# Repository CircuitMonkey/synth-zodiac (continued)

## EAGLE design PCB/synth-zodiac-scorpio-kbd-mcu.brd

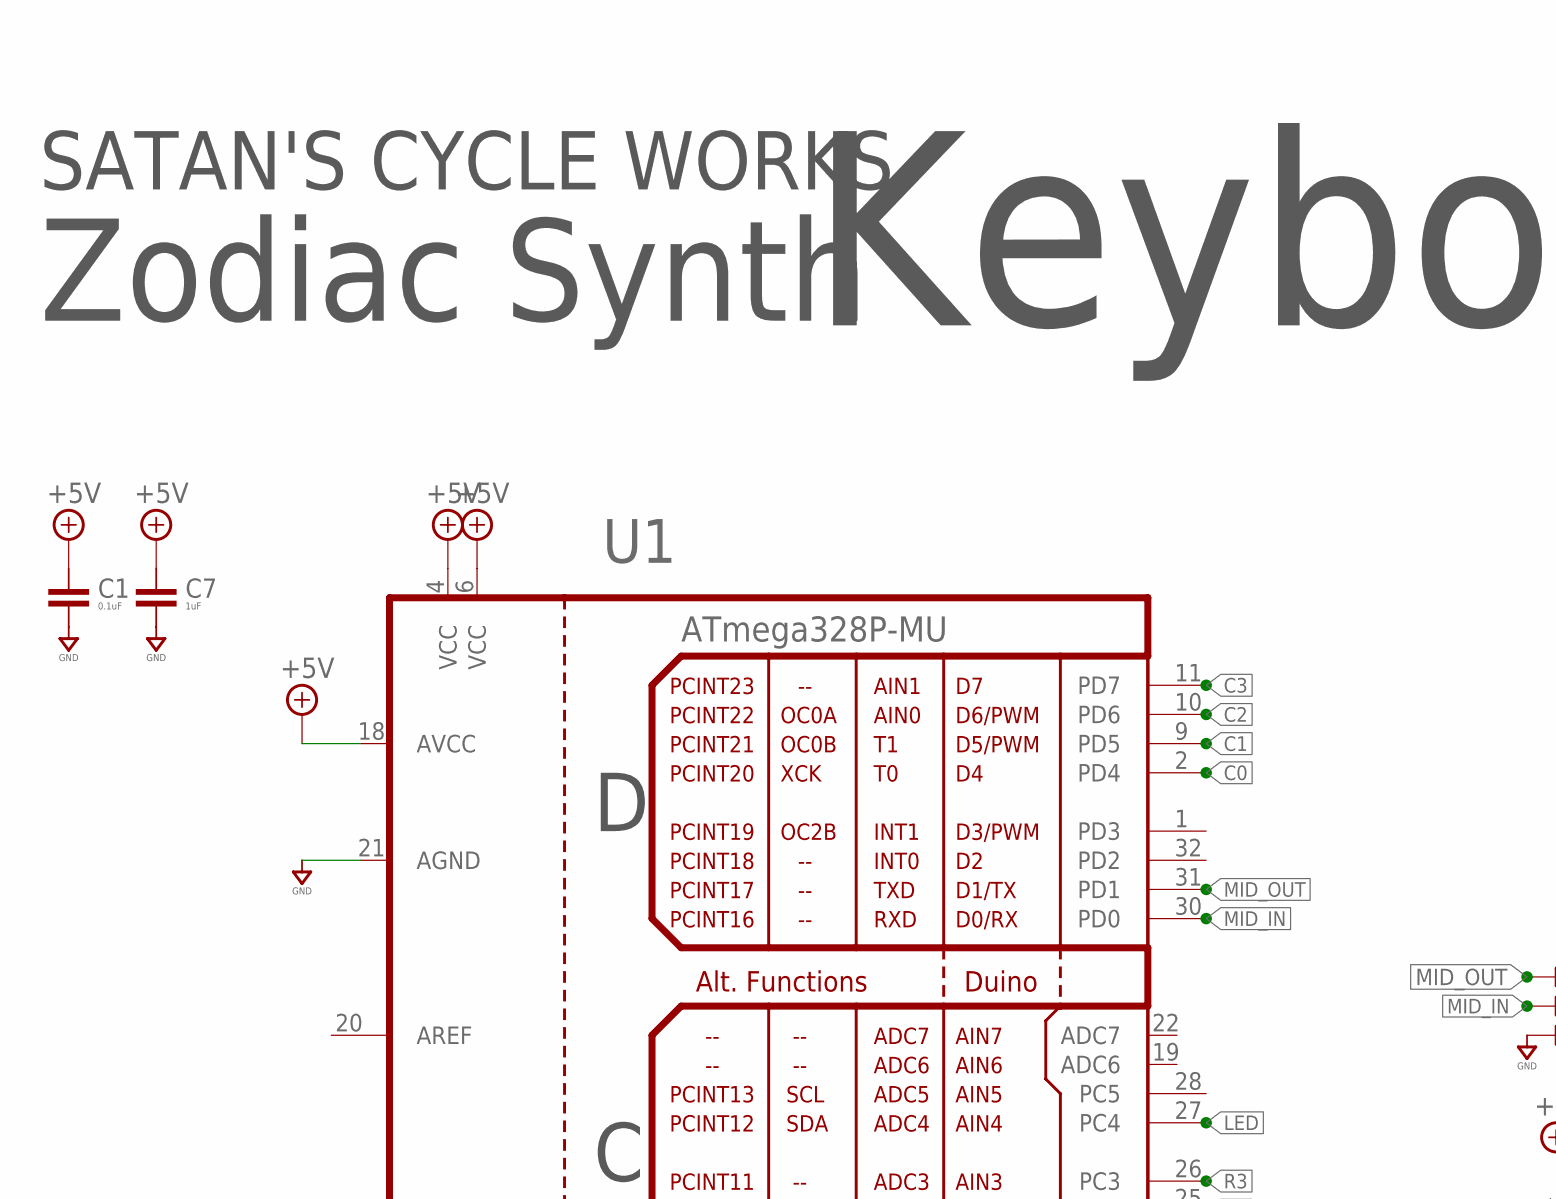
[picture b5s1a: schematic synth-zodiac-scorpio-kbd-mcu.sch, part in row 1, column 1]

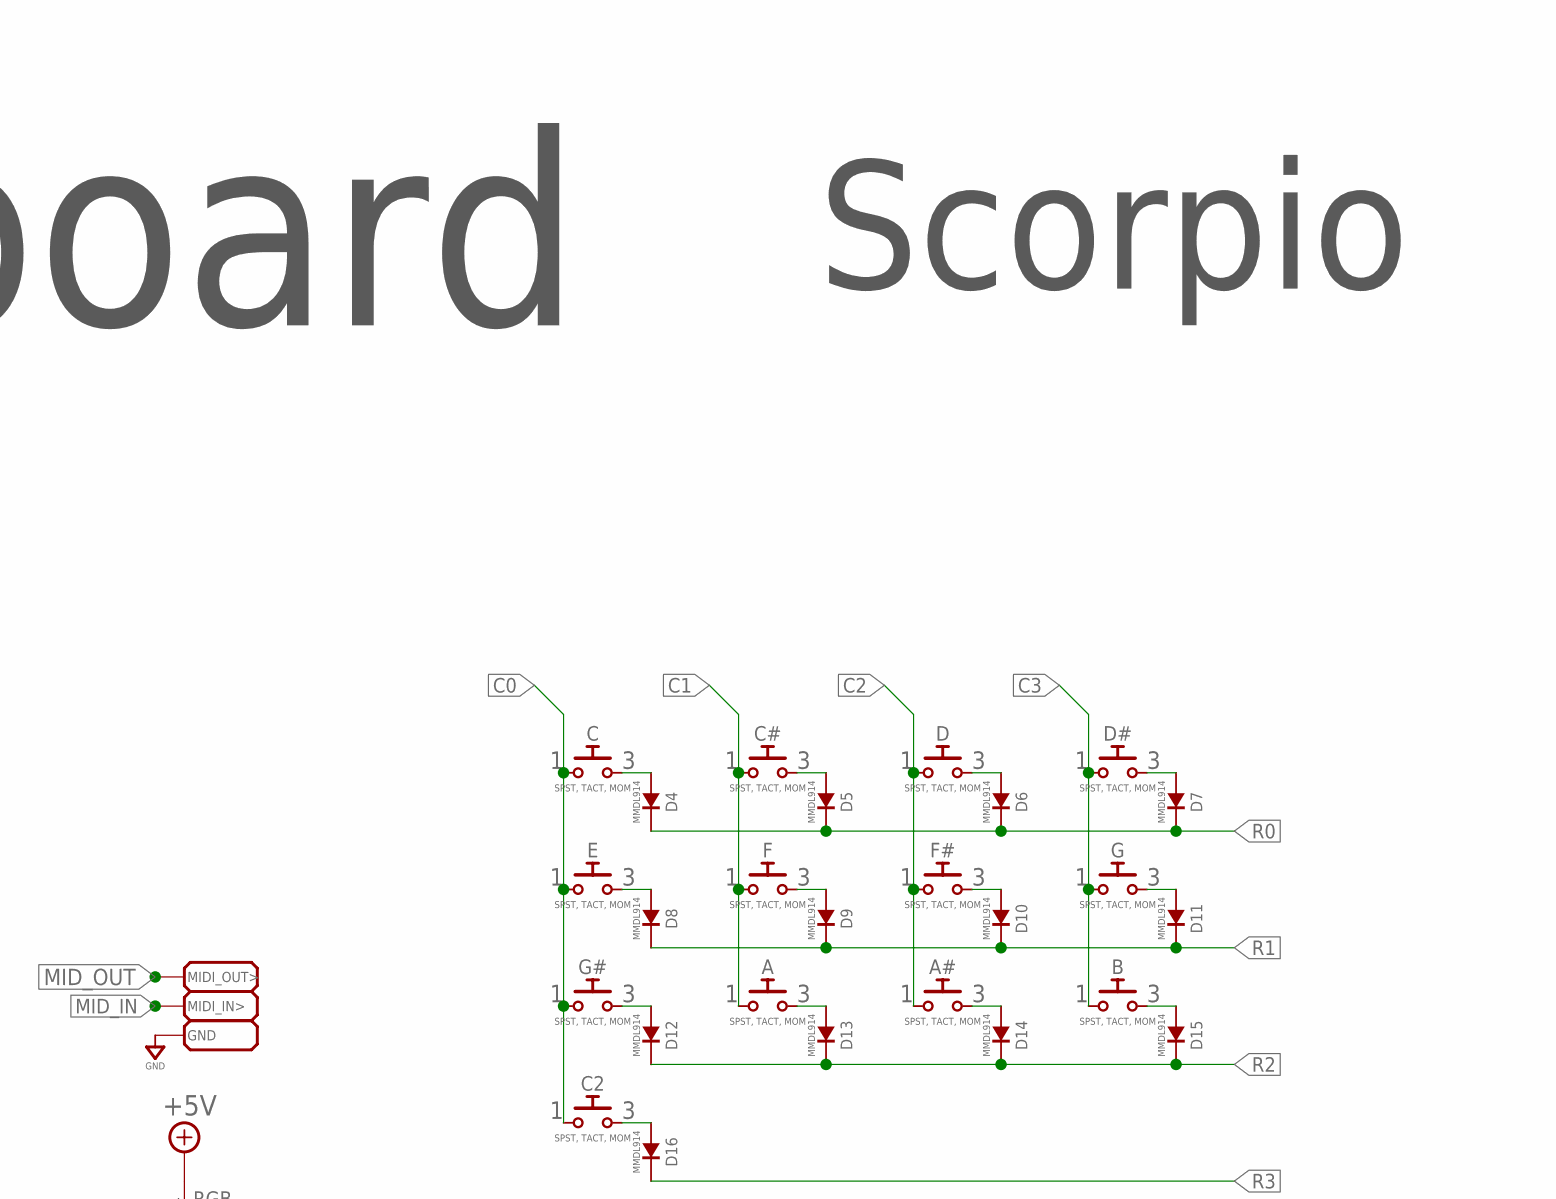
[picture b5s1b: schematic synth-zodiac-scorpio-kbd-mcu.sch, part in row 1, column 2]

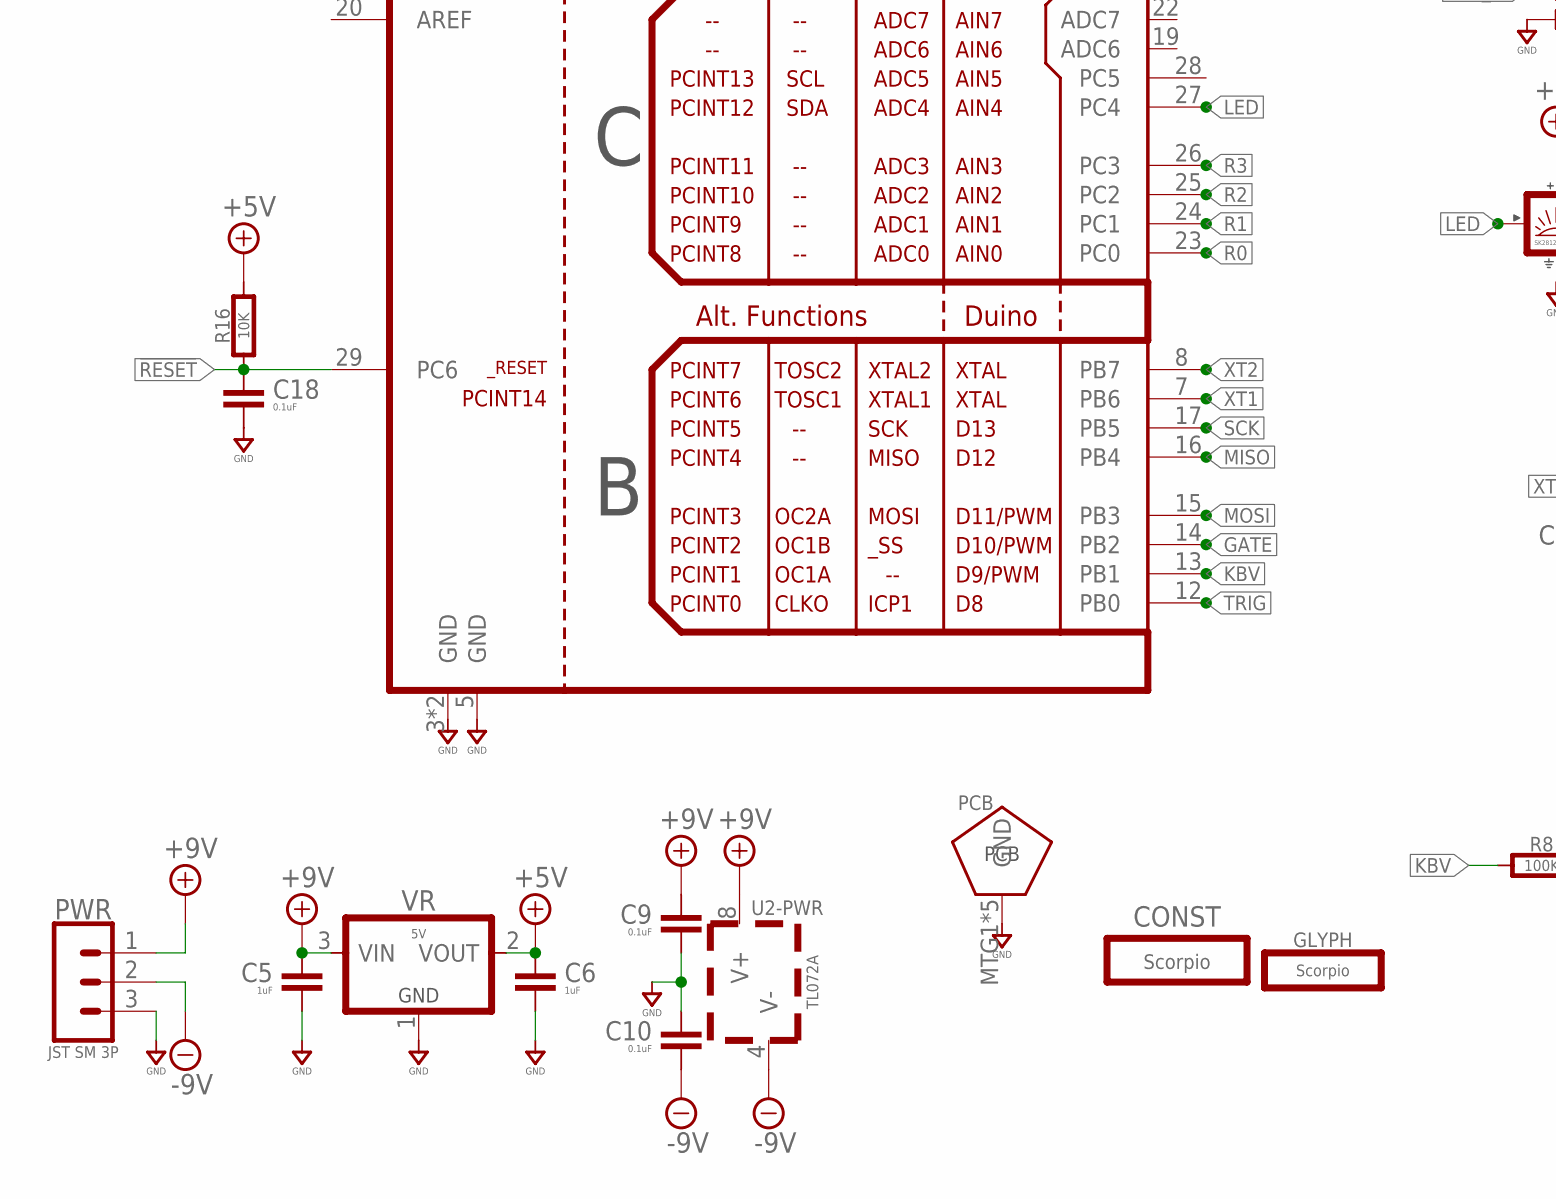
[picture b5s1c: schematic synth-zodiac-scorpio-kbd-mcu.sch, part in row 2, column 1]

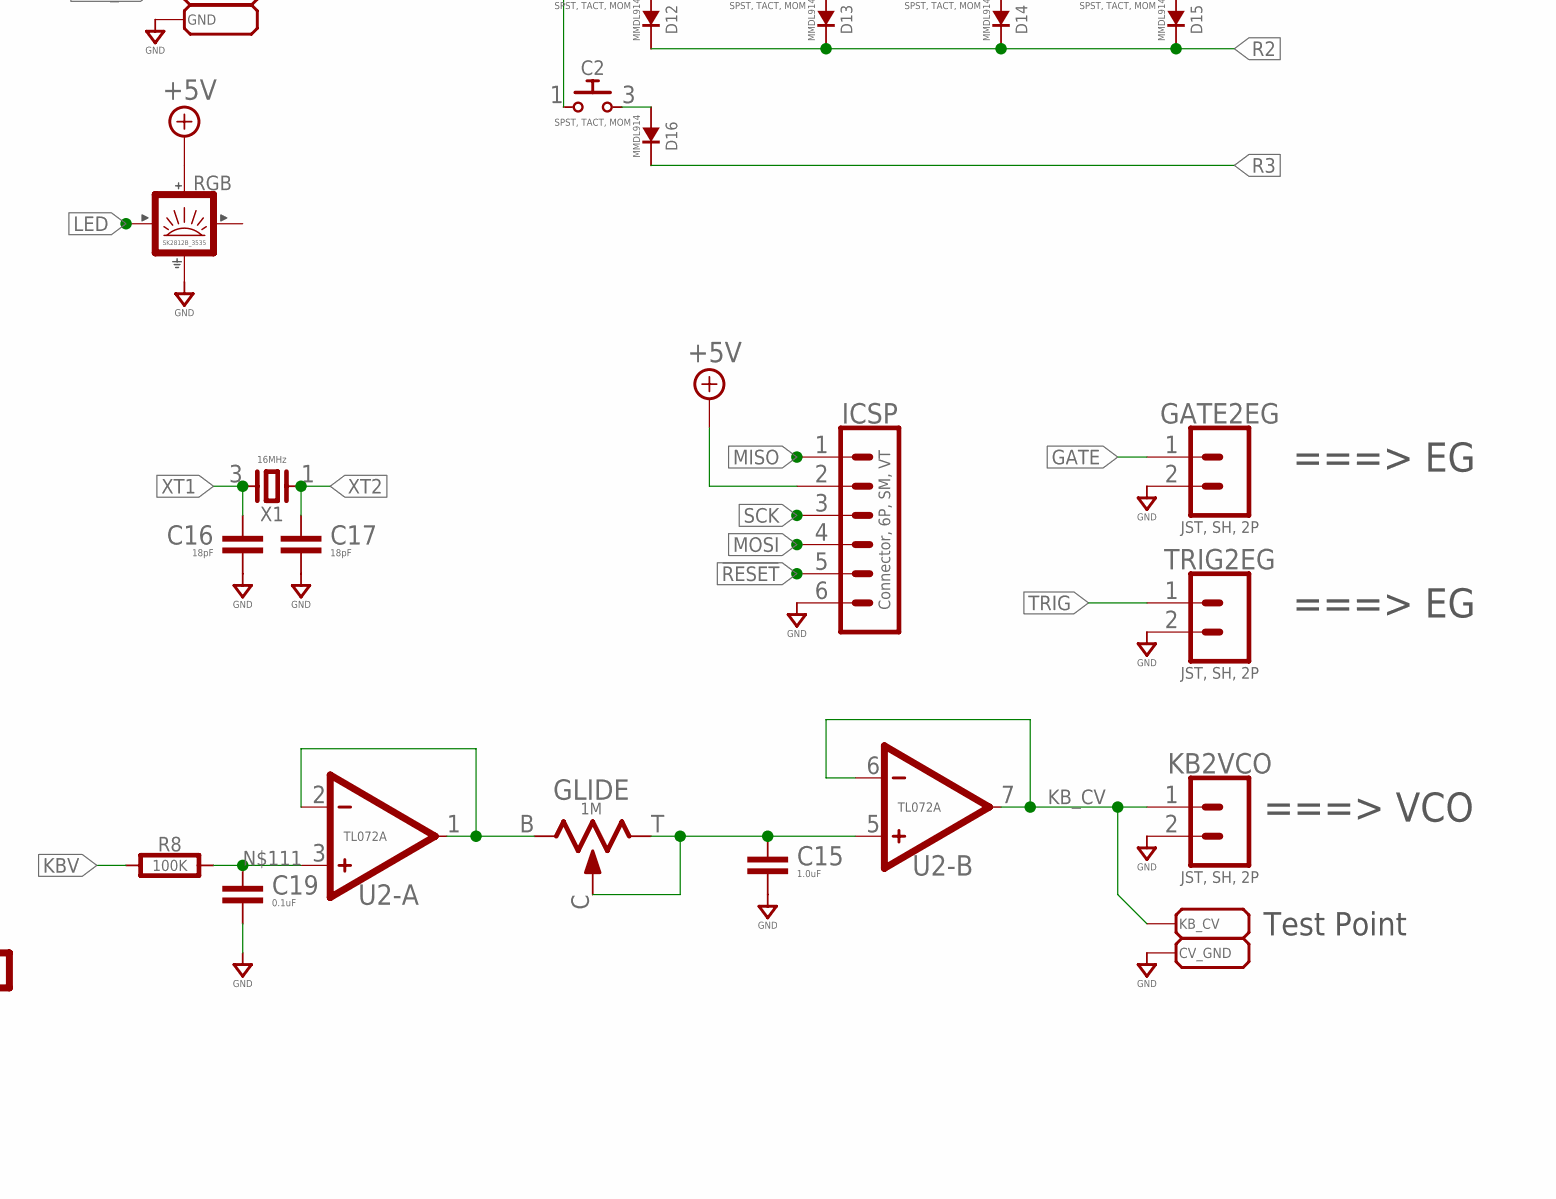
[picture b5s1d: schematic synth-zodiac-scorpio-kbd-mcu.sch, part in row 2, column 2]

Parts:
A: SPST, TACT, MOM; B3FS-BACKMOUNT
A#: SPST, TACT, MOM; B3FS-BACKMOUNT
B: SPST, TACT, MOM; B3FS-BACKMOUNT
C, C2: SPST, TACT, MOM; B3FS-BACKMOUNT
C1, C9, C10, C18, C19: 0.1uF; 0603-CAP
C5, C6, C7: 1uF; 0603-CAP
C15: 1.0uF; 0603-CAP
C16, C17: 18pF; 0603-CAP
C#: SPST, TACT, MOM; B3FS-BACKMOUNT
CONST: Scorpio; SCORPIO-CONST
CV_GND: PAD-70X70SMD-070X070; SMD-070MIL
D: SPST, TACT, MOM; B3FS-BACKMOUNT
D4, D5, D6, D7, D8, D9, D10, D11, D12, D13, D14, D15, D16: MMDL914; SOD-323
D#: SPST, TACT, MOM; B3FS-BACKMOUNT
E: SPST, TACT, MOM; B3FS-BACKMOUNT
F: SPST, TACT, MOM; B3FS-BACKMOUNT
F#: SPST, TACT, MOM; B3FS-BACKMOUNT
G: SPST, TACT, MOM; B3FS-BACKMOUNT
G#: SPST, TACT, MOM; B3FS-BACKMOUNT
GATE2EG: JST, SH, 2P; BM02B-SRSS-TB
GLIDE: 1M; POT-RV9110
GLYPH: Scorpio; SCORPIO-GLYPH
GND: PAD-70X70SMD-070X070; SMD-070MIL
ICSP: Connector, 6P, SM, VT; BM06B-SRSS-TB
KB2VCO: JST, SH, 2P; BM02B-SRSS-TB
KB_CV: PAD-70X70SMD-070X070; SMD-070MIL
MIDI_IN>: PAD-70X70SMD-070X070; SMD-070MIL
MIDI_OUT>: PAD-70X70SMD-070X070; SMD-070MIL
PCB: PCB FAB; PENTAGON-40MM-RAD
PWR: JST SM 3P; BM03B-SRSS-TB
R8: 100K; 0603-RES
R16: 10K; 0603-RES
RGB: SK2812B_3535; SMD_3535
TRIG2EG: JST, SH, 2P; BM02B-SRSS-TB
U1: ATmega328P-MU; MLF32
U2: TL072A; SOP08
VR: 5V; SOT-23
X1: 16MHz; 32X25

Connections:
!RESET: C18.1, ICSP.5, R16.1, U1.29 (PC6)
+5V: C1.1, C6.1, C7.1, ICSP.2, R16.2, RGB.4 (VDD), U1.4 (VCC), U1.6 (VCC), U1.18 (AVCC), VR.2 (VOUT)
+9V: C5.1, C9.1, PWR.1, U2.8 (V+), VR.3 (VIN)
-9V: C10.2, PWR.2, U2.4 (V-)
C0: C.1, C2.1, E.1, G#.1, U1.2 (PD4)
C1: A.1, C#.1, F.1, U1.9 (PD5)
C2: A#.1, D.1, F#.1, U1.10 (PD6)
C3: B.1, D#.1, G.1, U1.11 (PD7)
GATE: GATE2EG.1, U1.14 (PB2)
GND: C1.2, C5.2, C6.2, C7.2, C9.2, C10.1, C15.2, C16.2, C17.2, C18.2, C19.2, CV_GND.1, GATE2EG.2, GND.1, ICSP.6, KB2VCO.2, PCB.MTG1, PCB.MTG2, PCB.MTG3, PCB.MTG4, PCB.MTG5, PWR.3, RGB.2 (GND), TRIG2EG.2, U1.3 (GND), U1.5 (GND), U1.21 (AGND), U1.PAD (GND), VR.1 (GND)
KBV: R8.1, U1.13 (PB1)
KB_CV: KB2VCO.1, KB_CV.1, U2.6 (-), U2.7 (OUT)
LED: RGB.3 (IN), U1.27 (PC4)
MID_IN: MIDI_IN>.1, U1.30 (PD0)
MID_OUT: MIDI_OUT>.1, U1.31 (PD1)
MISO: ICSP.1, U1.16 (PB4)
MOSI: ICSP.4, U1.15 (PB3)
unnamed: C19.1, R8.2, U2.3 (+)
unnamed: GLIDE.B (1), U2.1 (OUT), U2.2 (-)
unnamed: C.3 (2), D4.A
unnamed: C15.1, GLIDE.C (2), GLIDE.T (3), U2.5 (+)
unnamed: C#.3 (2), D5.A
unnamed: D.3 (2), D6.A
unnamed: D7.A, D#.3 (2)
unnamed: D8.A, E.3 (2)
unnamed: D9.A, F.3 (2)
unnamed: D10.A, F#.3 (2)
unnamed: D11.A, G.3 (2)
unnamed: D12.A, G#.3 (2)
unnamed: A.3 (2), D13.A
unnamed: A#.3 (2), D14.A
unnamed: B.3 (2), D15.A
unnamed: C2.3 (2), D16.A
R0: D4.K, D5.K, D6.K, D7.K, U1.23 (PC0)
R1: D8.K, D9.K, D10.K, D11.K, U1.24 (PC1)
R2: D12.K, D13.K, D14.K, D15.K, U1.25 (PC2)
R3: D16.K, U1.26 (PC3)
SCK: ICSP.3, U1.17 (PB5)
TRIG: TRIG2EG.1, U1.12 (PB0)
XT1: C16.1, U1.7 (PB6), X1.3
XT2: C17.1, U1.8 (PB7), X1.1

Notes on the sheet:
===> EG
===> VCO
Test Point
Keyboard
Zodiac Synth
Scorpio
SATAN'S CYCLE WORKS

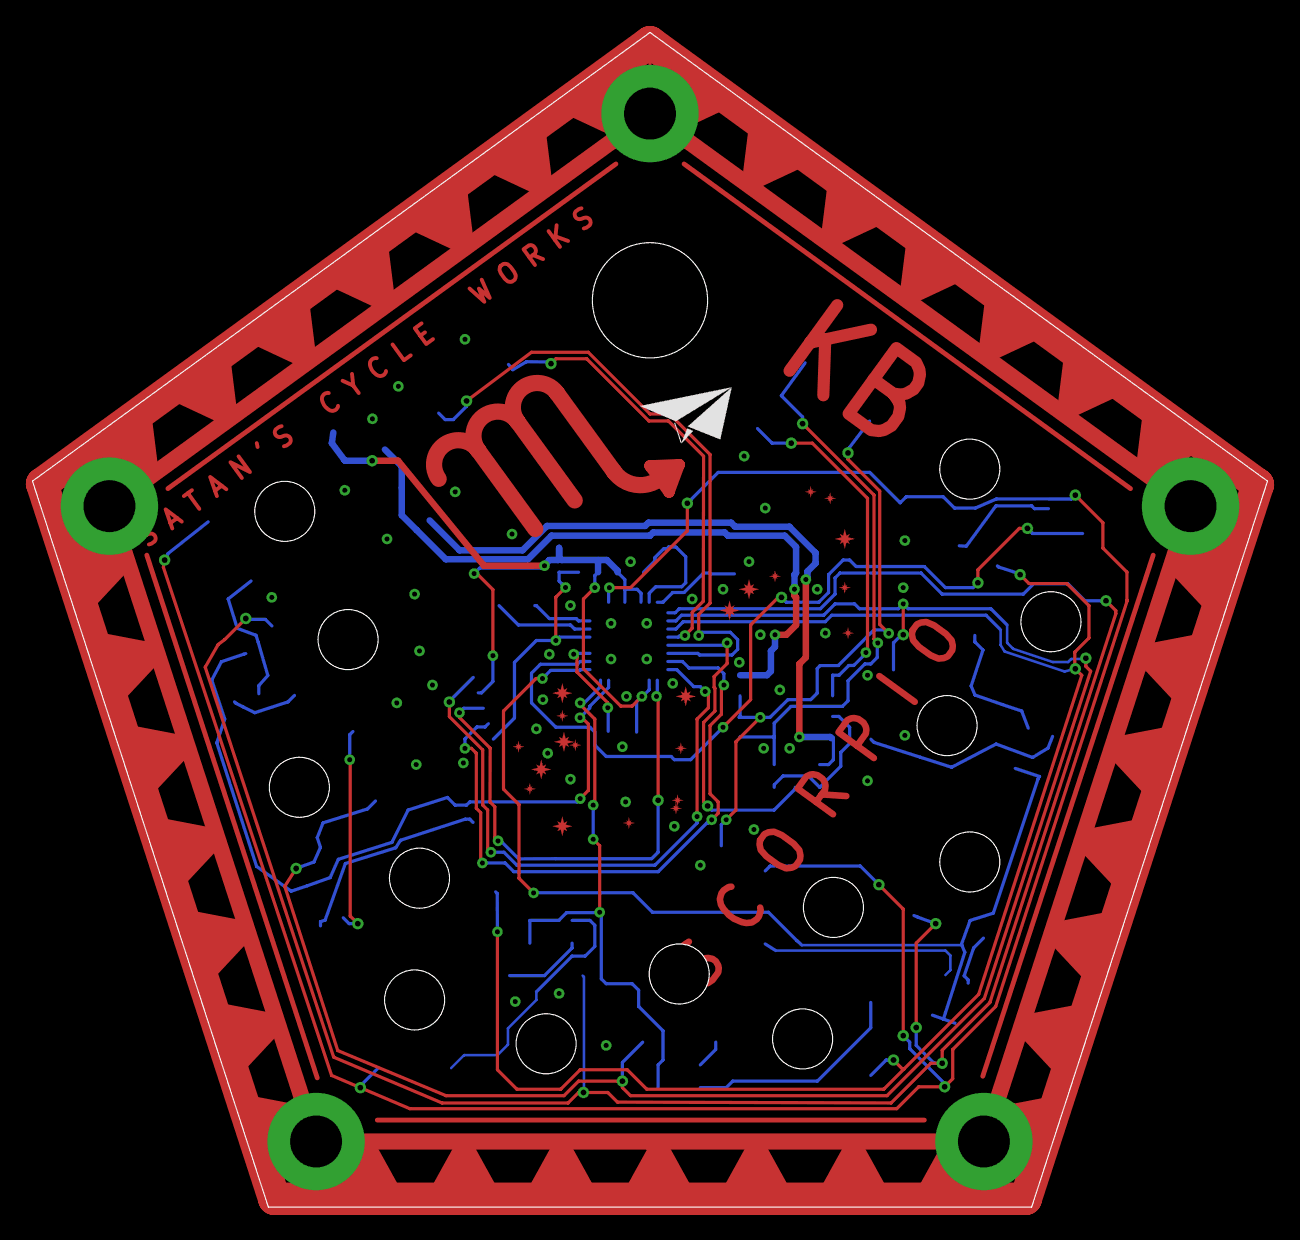
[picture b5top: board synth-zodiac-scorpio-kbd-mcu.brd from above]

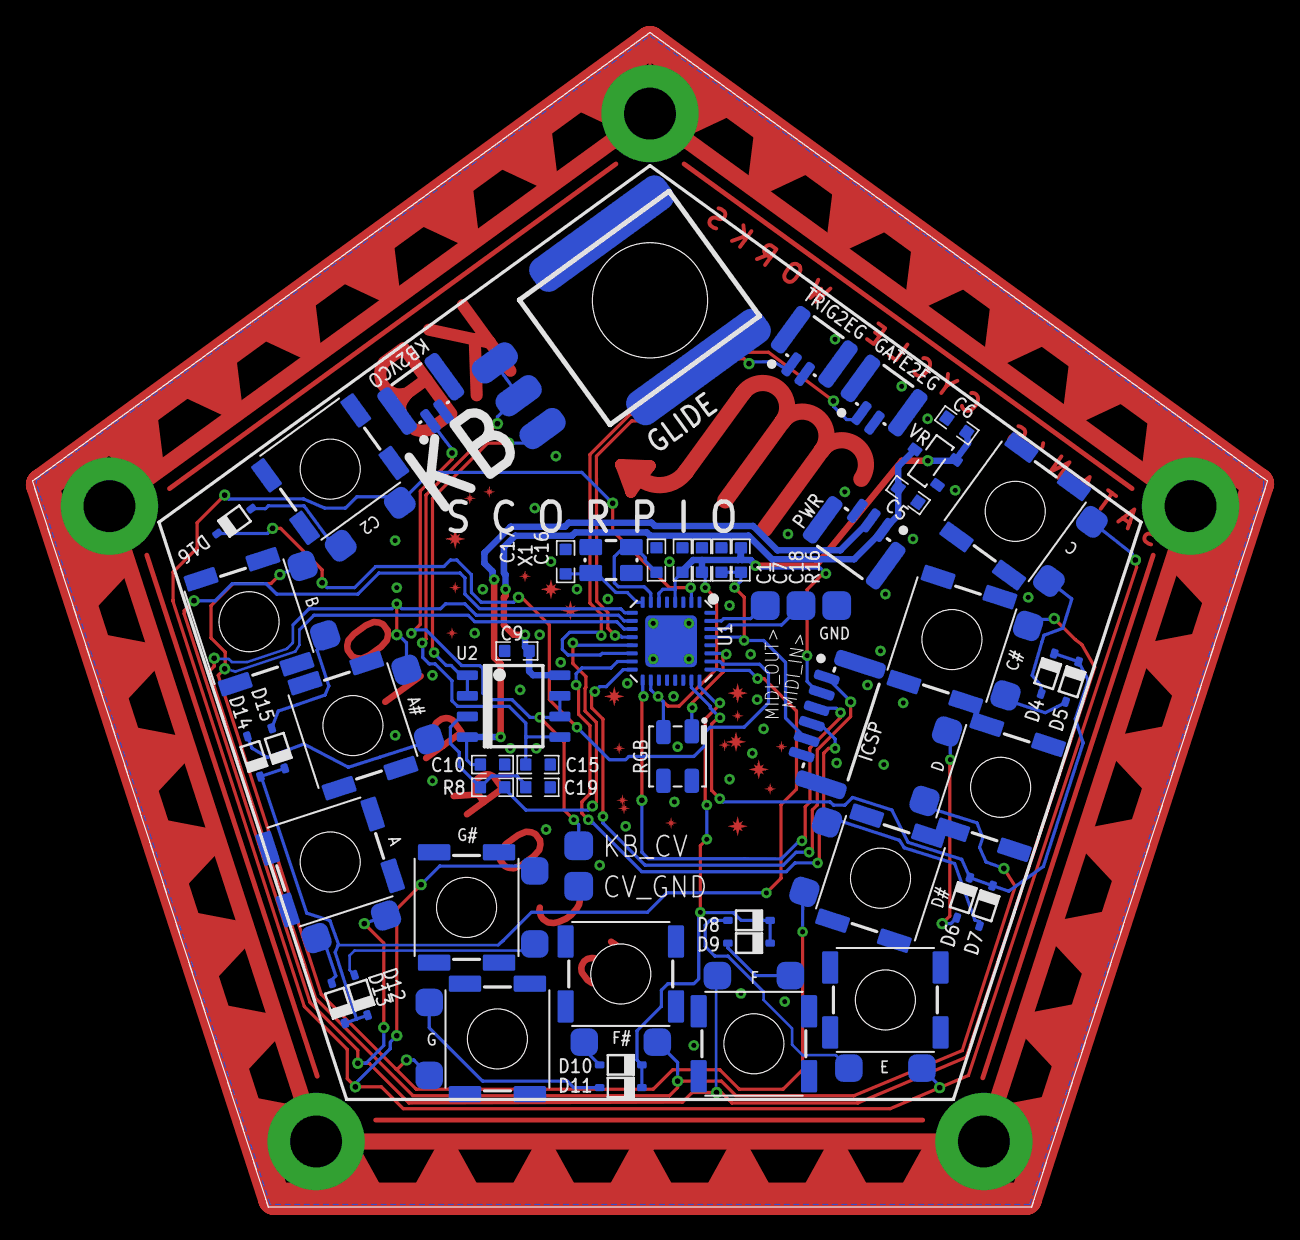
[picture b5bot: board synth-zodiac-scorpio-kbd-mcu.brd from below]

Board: 2 copper layers, 76.1 x 72.4 mm, 58 parts (42 on the bottom side), 41 nets.

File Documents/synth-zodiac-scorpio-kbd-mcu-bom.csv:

"Part";"Value";"Device";"Package";"Description";"COST01";"COST10";"COST100";"MFR";"MPN";"MPN2";"OC_MOUSER";"OC_SEEED";"SKU";"VALUE";
"A";"SPST, TACT, MOM";"PUSHBTN-MOMB3FS-BLIND";"B3FS-BACKMOUNT";"Pushbutton Switch";"0.15";"0.12";"0.09";"CK";"B3FS";"Tayda A-3961(2.3mm), A-5134(3.14mm,RA)";"";"";"";"SPST, TACT, MOM";
"A#";"SPST, TACT, MOM";"PUSHBTN-MOMB3FS-BLIND";"B3FS-BACKMOUNT";"Pushbutton Switch";"0.15";"0.12";"0.09";"CK";"B3FS";"Tayda A-3961(2.3mm), A-5134(3.14mm,RA)";"";"";"";"SPST, TACT, MOM";
"B";"SPST, TACT, MOM";"PUSHBTN-MOMB3FS-BLIND";"B3FS-BACKMOUNT";"Pushbutton Switch";"0.15";"0.12";"0.09";"CK";"B3FS";"Tayda A-3961(2.3mm), A-5134(3.14mm,RA)";"";"";"";"SPST, TACT, MOM";
"C";"SPST, TACT, MOM";"PUSHBTN-MOMB3FS-BLIND";"B3FS-BACKMOUNT";"Pushbutton Switch";"0.15";"0.12";"0.09";"CK";"B3FS";"Tayda A-3961(2.3mm), A-5134(3.14mm,RA)";"";"";"";"SPST, TACT, MOM";
"C#";"SPST, TACT, MOM";"PUSHBTN-MOMB3FS-BLIND";"B3FS-BACKMOUNT";"Pushbutton Switch";"0.15";"0.12";"0.09";"CK";"B3FS";"Tayda A-3961(2.3mm), A-5134(3.14mm,RA)";"";"";"";"SPST, TACT, MOM";
"C1";"0.1uF";"CAPACITOR0603";"0603-CAP";"Capacitor";"0.12";"0.09";"0.05";"";"";"";"";"";"";"";
"C2";"SPST, TACT, MOM";"PUSHBTN-MOMB3FS-BLIND";"B3FS-BACKMOUNT";"Pushbutton Switch";"0.15";"0.12";"0.09";"CK";"B3FS";"Tayda A-3961(2.3mm), A-5134(3.14mm,RA)";"";"";"";"SPST, TACT, MOM";
"C5";"1uF";"CAPACITOR0603";"0603-CAP";"Capacitor";"0.12";"0.09";"0.05";"";"";"";"";"";"";"";
"C6";"1uF";"CAPACITOR0603";"0603-CAP";"Capacitor";"0.12";"0.09";"0.05";"";"";"";"";"";"";"";
"C7";"1uF";"CAPACITOR0603";"0603-CAP";"Capacitor";"0.12";"0.09";"0.05";"";"";"";"";"";"";"";
"C9";"0.1uF";"CAPACITOR0603";"0603-CAP";"Capacitor";"0.12";"0.09";"0.05";"";"";"";"";"";"";"";
"C10";"0.1uF";"CAPACITOR0603";"0603-CAP";"Capacitor";"0.12";"0.09";"0.05";"";"";"";"";"";"";"";
"C15";"1.0uF";"CAPACITOR0603";"0603-CAP";"Capacitor";"0.12";"0.09";"0.05";"";"";"";"";"";"";"";
"C16";"18pF";"CAPACITOR0603";"0603-CAP";"Capacitor";"0.12";"0.09";"0.05";"";"";"";"";"";"";"";
"C17";"18pF";"CAPACITOR0603";"0603-CAP";"Capacitor";"0.12";"0.09";"0.05";"";"";"";"";"";"";"";
"C18";"0.1uF";"CAPACITOR0603";"0603-CAP";"Capacitor";"0.12";"0.09";"0.05";"";"";"";"";"";"";"";
"C19";"0.1uF";"CAPACITOR0603";"0603-CAP";"Capacitor";"0.12";"0.09";"0.05";"";"";"";"";"";"";"";
"CONST";"Scorpio";"CONSTELLATION-SCORPIO";"SCORPIO-CONST";"Constellations";"";"";"";"";"";"";"";"";"";"Scorpio";
"CV_GND";"PAD-70X70SMD-070X070";"PAD-70X70SMD-070X070";"SMD-070MIL";"Solder Pad";"";"";"";"";"";"";"";"";"";"";
"D";"SPST, TACT, MOM";"PUSHBTN-MOMB3FS-BLIND";"B3FS-BACKMOUNT";"Pushbutton Switch";"0.15";"0.12";"0.09";"CK";"B3FS";"Tayda A-3961(2.3mm), A-5134(3.14mm,RA)";"";"";"";"SPST, TACT, MOM";
"D#";"SPST, TACT, MOM";"PUSHBTN-MOMB3FS-BLIND";"B3FS-BACKMOUNT";"Pushbutton Switch";"0.15";"0.12";"0.09";"CK";"B3FS";"Tayda A-3961(2.3mm), A-5134(3.14mm,RA)";"";"";"";"SPST, TACT, MOM";
"D4";"MMDL914";"DIODE-SWITCHING-SOD323";"SOD-323";"Diode";"";"";"";"ON Semi";"MMDL914";"";"";"";"";"MMDL914";
"D5";"MMDL914";"DIODE-SWITCHING-SOD323";"SOD-323";"Diode";"";"";"";"ON Semi";"MMDL914";"";"";"";"";"MMDL914";
"D6";"MMDL914";"DIODE-SWITCHING-SOD323";"SOD-323";"Diode";"";"";"";"ON Semi";"MMDL914";"";"";"";"";"MMDL914";
"D7";"MMDL914";"DIODE-SWITCHING-SOD323";"SOD-323";"Diode";"";"";"";"ON Semi";"MMDL914";"";"";"";"";"MMDL914";
"D8";"MMDL914";"DIODE-SWITCHING-SOD323";"SOD-323";"Diode";"";"";"";"ON Semi";"MMDL914";"";"";"";"";"MMDL914";
"D9";"MMDL914";"DIODE-SWITCHING-SOD323";"SOD-323";"Diode";"";"";"";"ON Semi";"MMDL914";"";"";"";"";"MMDL914";
"D10";"MMDL914";"DIODE-SWITCHING-SOD323";"SOD-323";"Diode";"";"";"";"ON Semi";"MMDL914";"";"";"";"";"MMDL914";
"D11";"MMDL914";"DIODE-SWITCHING-SOD323";"SOD-323";"Diode";"";"";"";"ON Semi";"MMDL914";"";"";"";"";"MMDL914";
"D12";"MMDL914";"DIODE-SWITCHING-SOD323";"SOD-323";"Diode";"";"";"";"ON Semi";"MMDL914";"";"";"";"";"MMDL914";
"D13";"MMDL914";"DIODE-SWITCHING-SOD323";"SOD-323";"Diode";"";"";"";"ON Semi";"MMDL914";"";"";"";"";"MMDL914";
"D14";"MMDL914";"DIODE-SWITCHING-SOD323";"SOD-323";"Diode";"";"";"";"ON Semi";"MMDL914";"";"";"";"";"MMDL914";
"D15";"MMDL914";"DIODE-SWITCHING-SOD323";"SOD-323";"Diode";"";"";"";"ON Semi";"MMDL914";"";"";"";"";"MMDL914";
"D16";"MMDL914";"DIODE-SWITCHING-SOD323";"SOD-323";"Diode";"";"";"";"ON Semi";"MMDL914";"";"";"";"";"MMDL914";
"E";"SPST, TACT, MOM";"PUSHBTN-MOMB3FS-BLIND";"B3FS-BACKMOUNT";"Pushbutton Switch";"0.15";"0.12";"0.09";"CK";"B3FS";"Tayda A-3961(2.3mm), A-5134(3.14mm,RA)";"";"";"";"SPST, TACT, MOM";
"F";"SPST, TACT, MOM";"PUSHBTN-MOMB3FS-BLIND";"B3FS-BACKMOUNT";"Pushbutton Switch";"0.15";"0.12";"0.09";"CK";"B3FS";"Tayda A-3961(2.3mm), A-5134(3.14mm,RA)";"";"";"";"SPST, TACT, MOM";
"F#";"SPST, TACT, MOM";"PUSHBTN-MOMB3FS-BLIND";"B3FS-BACKMOUNT";"Pushbutton Switch";"0.15";"0.12";"0.09";"CK";"B3FS";"Tayda A-3961(2.3mm), A-5134(3.14mm,RA)";"";"";"";"SPST, TACT, MOM";
"G";"SPST, TACT, MOM";"PUSHBTN-MOMB3FS-BLIND";"B3FS-BACKMOUNT";"Pushbutton Switch";"0.15";"0.12";"0.09";"CK";"B3FS";"Tayda A-3961(2.3mm), A-5134(3.14mm,RA)";"";"";"";"SPST, TACT, MOM";
"G#";"SPST, TACT, MOM";"PUSHBTN-MOMB3FS-BLIND";"B3FS-BACKMOUNT";"Pushbutton Switch";"0.15";"0.12";"0.09";"CK";"B3FS";"Tayda A-3961(2.3mm), A-5134(3.14mm,RA)";"";"";"";"SPST, TACT, MOM";
"GATE2EG";"JST, SH, 2P";"02P-SM-VT-SMT";"BM02B-SRSS-TB";"2 pin connector";"0.45";"0.4";"0.35";"JST";"BMB02B-SRSS-TB";"";"";"";"";"JST, SH, 2P";
"GLIDE";"1M";"TRIMPOT9MM_PCB_SHAFT";"POT-RV9110";"Potentiometer";"0.70";"0.60";"0.60";"Tayda";"RV9110NO-OS15A00";"";"";"";"A-5517";"";
"GLYPH";"Scorpio";"GLYPH-SCORPIO";"SCORPIO-GLYPH";"Glyph";"";"";"";"";"";"";"";"";"";"Scorpio";
"GND";"PAD-70X70SMD-070X070";"PAD-70X70SMD-070X070";"SMD-070MIL";"Solder Pad";"";"";"";"";"";"";"";"";"";"";
"ICSP";"Connector, 6P, SM, VT";"06P-SM-VT-SMT";"BM06B-SRSS-TB";"Connector, 6P";"0.60";"0.52";"0.49";"JST";"BM06-SRSS-TB";"";"";"";"";"Connector, 6P, SM, VT";
"KB2VCO";"JST, SH, 2P";"02P-SM-VT-SMT";"BM02B-SRSS-TB";"2 pin connector";"0.45";"0.4";"0.35";"JST";"BMB02B-SRSS-TB";"";"";"";"";"JST, SH, 2P";
"KB_CV";"PAD-70X70SMD-070X070";"PAD-70X70SMD-070X070";"SMD-070MIL";"Solder Pad";"";"";"";"";"";"";"";"";"";"";
"MIDI_IN>";"PAD-70X70SMD-070X070";"PAD-70X70SMD-070X070";"SMD-070MIL";"Solder Pad";"";"";"";"";"";"";"";"";"";"";
"MIDI_OUT>";"PAD-70X70SMD-070X070";"PAD-70X70SMD-070X070";"SMD-070MIL";"Solder Pad";"";"";"";"";"";"";"";"";"";"";
"PCB";"PCB FAB";"PENTAGON-40R";"PENTAGON-40MM-RAD";"Pentagram shaped PCB";"";"";"";"";"";"";"";"";"";"PCB FAB";
"PWR";"JST SM 3P";"03P-SM-VT-SMT";"BM03B-SRSS-TB";"3 pin connector";"0.60";"0.45";"0.38";"JST";"BM03B-SRSS-TB";"";"";"";"";"JST SM 3P";
"R8";"100K";"RESISTOR0603";"0603-RES";"Resistor";"0.10";"0.05";"0.02";"";"";"";"";"";"";"";
"R16";"10.0M";"RESISTOR0603";"0603-RES";"Resistor";"0.10";"0.05";"0.02";"";"";"";"";"";"";"";
"RGB";"SK2812B_3535";"SMART_LED3535";"SMD_3535";"Smart LED  SK6812  WS2812";"0.60";"0.50";"0.40";"";"";"";"";"";"";"SK2812B_3535";
"TRIG2EG";"JST, SH, 2P";"02P-SM-VT-SMT";"BM02B-SRSS-TB";"2 pin connector";"0.45";"0.4";"0.35";"JST";"BMB02B-SRSS-TB";"";"";"";"";"JST, SH, 2P";
"U1";"ATmega328P-MU";"ATMEGA328MU";"MLF32";"Atmega 328P";"";"";"";"Atmel";"atmega328p-mu";"";"556-ATMEGA328P-MU";"310010005";"";"ATmega328P-MU";
"U2";"TL072A";"DUALTL072A";"SOP08";"Dual Op-Amp";"0.65";"0.55";"0.45";"ST";"TL072A";"";"";"";"";"TL072A";
"VR";"5V";"LDO-3P--5V-SOT23";"SOT-23";"regulator 3-pin";"0.66";"0.56";"0.39";"Diodes, Inc.";"AP7387-50SA";"";"";"";"";"5V";
"X1";"16MHz";"2P3.2X2.5";"32X25";"Crystal";"";"";"";"Epson";"FA-238 16.0000MB-K3";"";"";"";"";"16MHz";

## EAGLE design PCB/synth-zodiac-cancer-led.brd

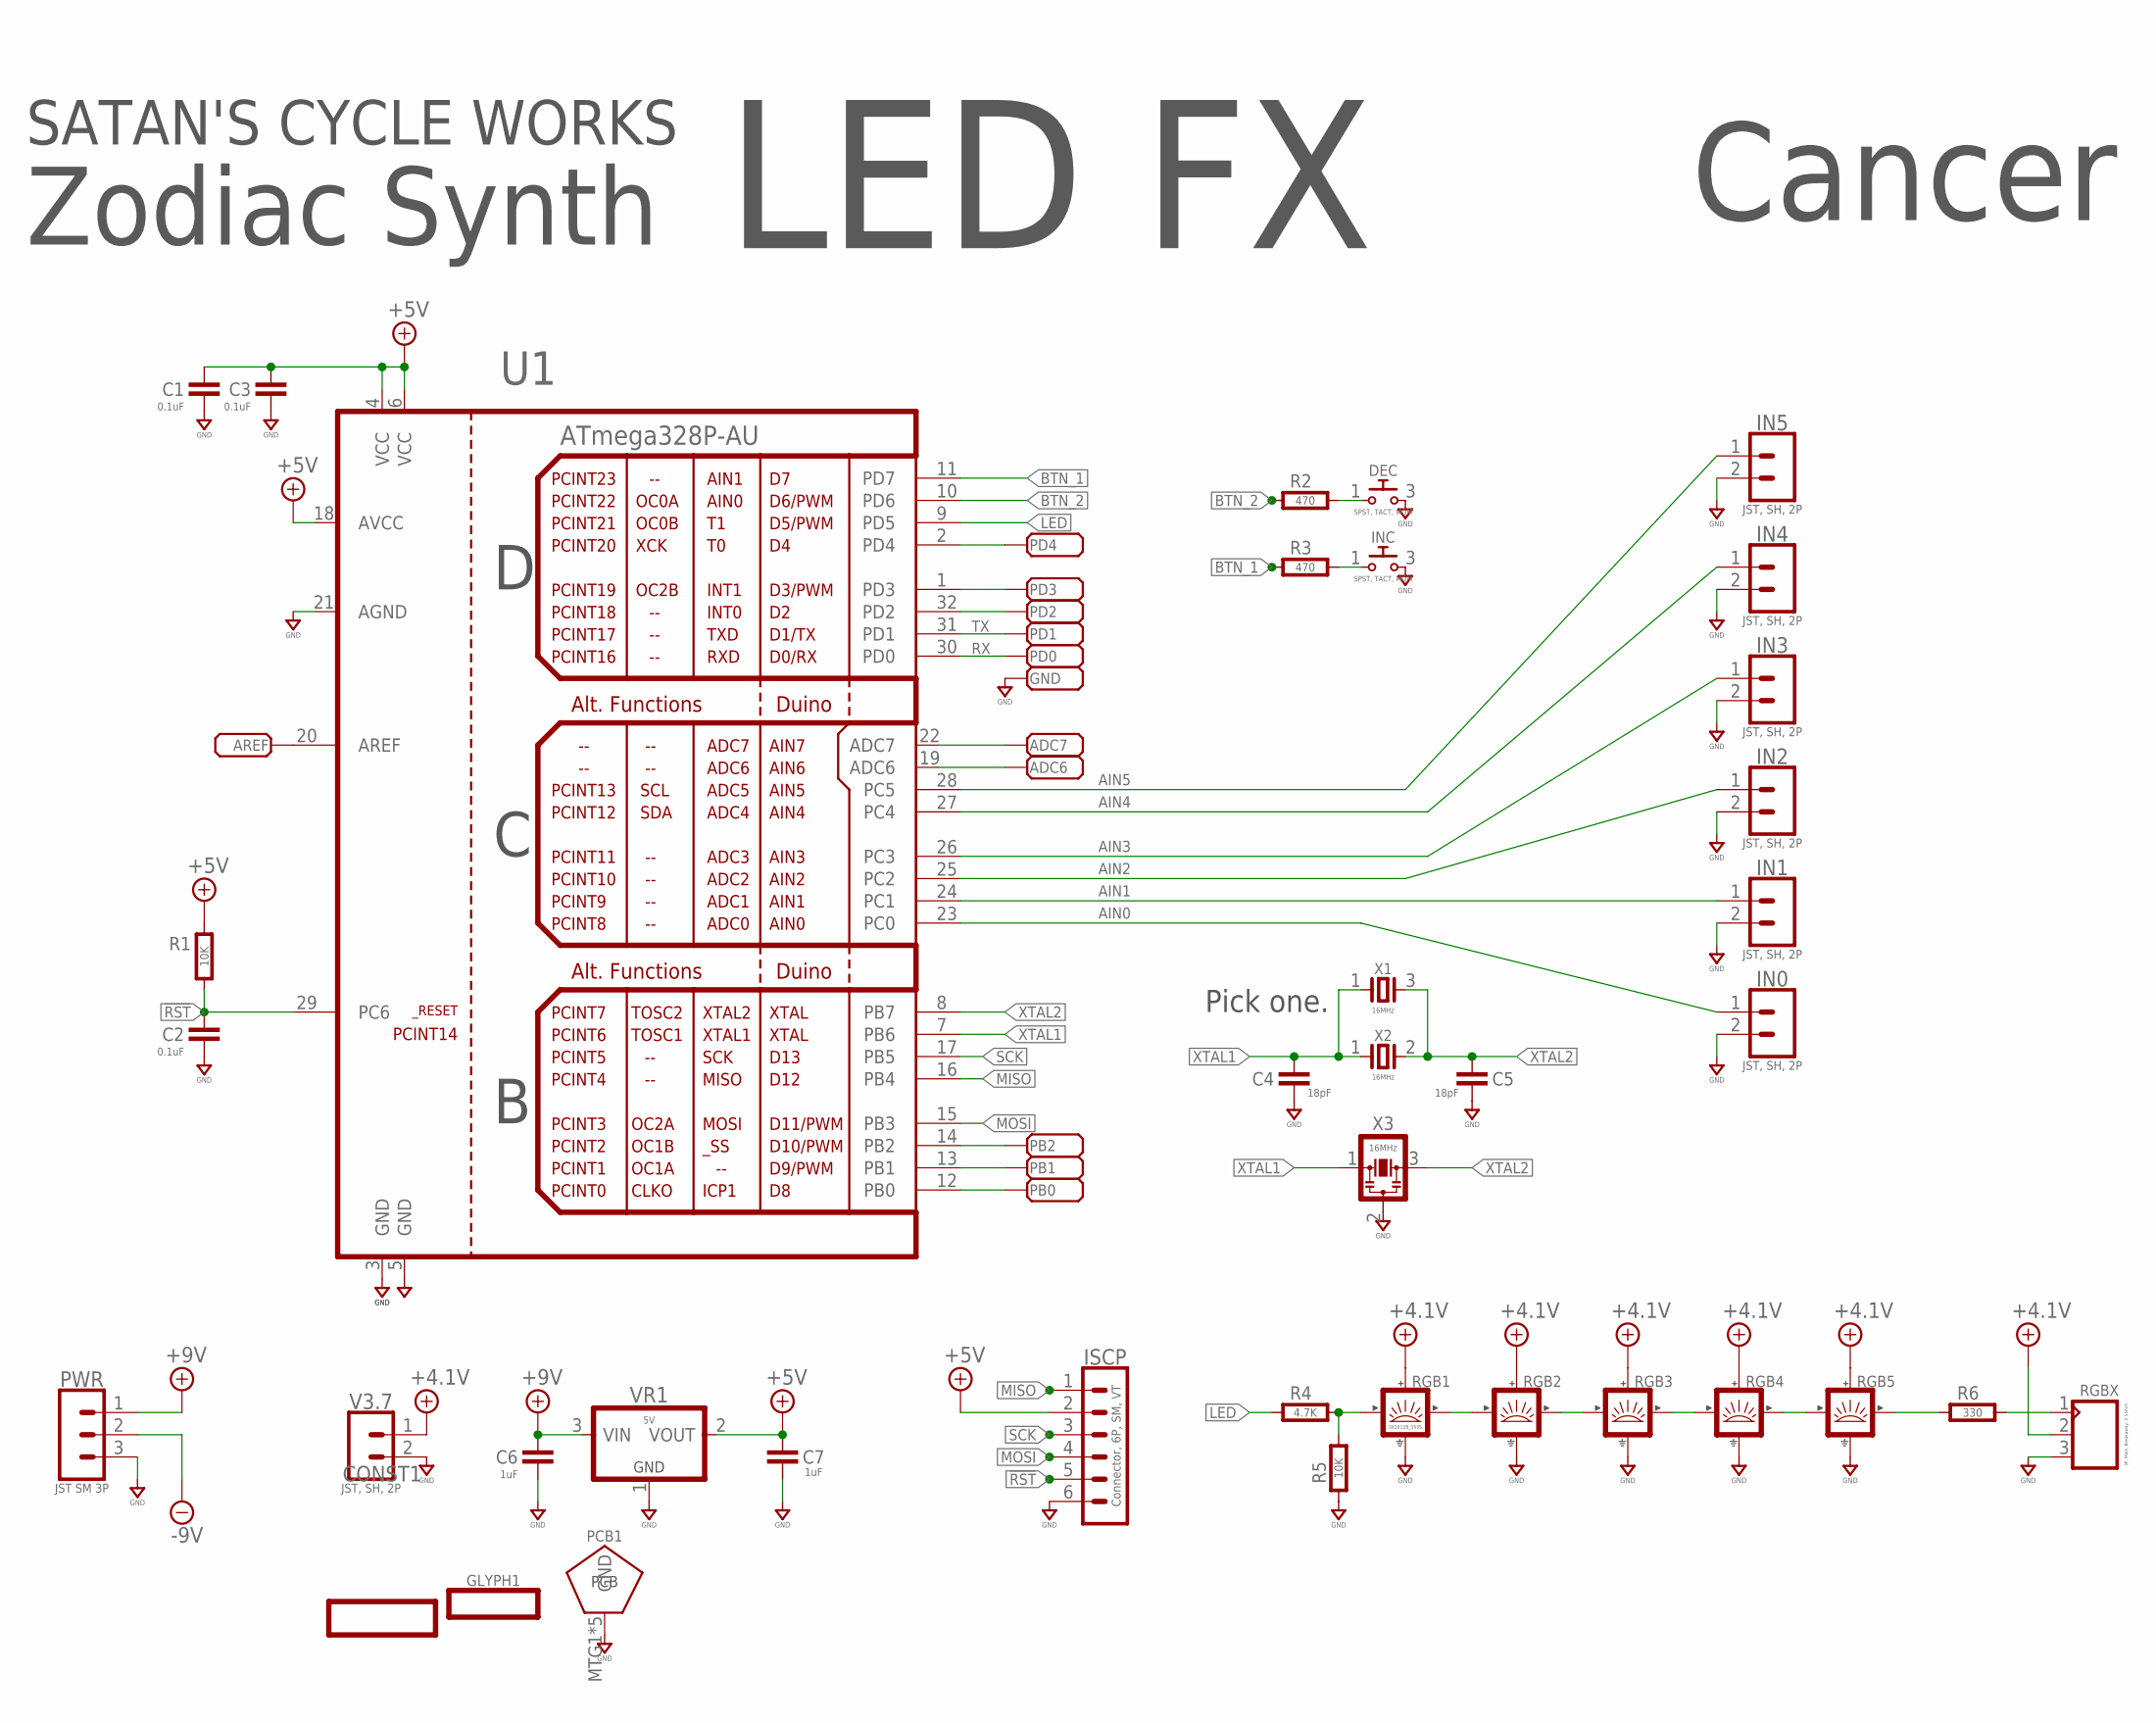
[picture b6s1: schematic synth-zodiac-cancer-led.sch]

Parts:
ADC6, ADC7: PADSMD-050X050; SMD-050X050
AREF: PADSMD-050X050; SMD-050X050
C1, C2, C3: 0.1uF; 0603-CAP
C4, C5: 18pF; 0603-CAP
C6, C7: 1uF; 0603-CAP
CONST1: CONSTELLATION-CANCER; CANCER-CONST
DEC: SPST, TACT, MOM; B3FS-BACKMOUNT
GLYPH1: GLYPH-CANCER; CANCER-GLYPH
GND: PADSMD-050X050; SMD-050X050
IN0, IN1, IN2, IN3, IN4, IN5: JST, SH, 2P; BM02B-SRSS-TB
INC: SPST, TACT, MOM; B3FS-BACKMOUNT
ISCP: Connector, 6P, SM, VT; BM06B-SRSS-TB
PB0, PB1, PB2: PADSMD-050X050; SMD-050X050
PCB1: PCB FAB; PENTAGON-40MM-RAD
PD0, PD1, PD2, PD3, PD4: PADSMD-050X050; SMD-050X050
PWR: JST SM 3P; BM03B-SRSS-TB
R1, R5: 10K; 0603-RES
R2, R3: 470; 0603-RES
R4: 4.7K; 0603-RES
R6: 330; 0603-RES
RGB1: SK2812B_3535; SMD_3535
RGB2, RGB3, RGB4, RGB5: SMART_LED4020-SIDE; SMD_4020
RGBX: 3P, Male, Breakaway, 2.54mm; MA03X1-EDGE-2.54MM
U1: ATmega328P-AU; TQFP-32-08
V3.7: JST, SH, 2P; BM02B-SRSS-TB
VR1: 5V; SOT-23
X1: 16MHz; 32X25
X2: 16MHz; CTS_5X3
X3: 16MHz; CSTE-RESONATOR

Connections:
!RST: C2.1, ISCP.5, R1.2, U1.29 (PC6)
+4.1V: RGB1.4 (VDD), RGB2.2 (VDD), RGB3.2 (VDD), RGB4.2 (VDD), RGB5.2 (VDD), RGBX.2, V3.7.1
+5V: C1.1, C3.1, C7.1, ISCP.2, R1.1, U1.4 (VCC), U1.6 (VCC), U1.18 (AVCC), VR1.2 (VOUT)
+9V: C6.1, PWR.1, VR1.3 (VIN)
-9V: PWR.2
AIN0: IN0.1, U1.23 (PC0)
AIN1: IN1.1, U1.24 (PC1)
AIN2: IN2.1, U1.25 (PC2)
AIN3: IN3.1, U1.26 (PC3)
AIN4: IN4.1, U1.27 (PC4)
AIN5: IN5.1, U1.28 (PC5)
BTN_1: R3.1, U1.11 (PD7)
BTN_2: R2.1, U1.10 (PD6)
GND: C1.2, C2.2, C3.2, C4.2, C5.2, C6.2, C7.2, DEC.3 (2), GND.1, IN0.2, IN1.2, IN2.2, IN3.2, IN4.2, IN5.2, INC.3 (2), ISCP.6, PCB1.MTG1, PCB1.MTG2, PCB1.MTG3, PCB1.MTG4, PCB1.MTG5, PWR.3, R5.1, RGB1.2 (GND), RGB2.4 (GND), RGB3.4 (GND), RGB4.4 (GND), RGB5.4 (GND), RGBX.3, U1.3 (GND), U1.5 (GND), U1.21 (AGND), V3.7.2, VR1.1 (GND), X3.2
LED: R4.1, U1.9 (PD5)
MISO: ISCP.1, U1.16 (PB4)
MOSI: ISCP.4, U1.15 (PB3)
unnamed: INC.1, R3.2
unnamed: RGB1.1 (OUT), RGB2.1 (IN)
unnamed: RGB2.3 (OUT), RGB3.1 (IN)
unnamed: RGB3.3 (OUT), RGB4.1 (IN)
unnamed: RGB4.3 (OUT), RGB5.1 (IN)
unnamed: R6.2, RGBX.1
unnamed: R4.2, R5.2, RGB1.3 (IN)
unnamed: PD4.1, U1.2 (PD4)
unnamed: R6.1, RGB5.3 (OUT)
unnamed: DEC.1, R2.2
unnamed: PD3.1, U1.1 (PD3)
unnamed: PD2.1, U1.32 (PD2)
unnamed: PB2.1, U1.14 (PB2)
unnamed: PB1.1, U1.13 (PB1)
unnamed: PB0.1, U1.12 (PB0)
unnamed: ADC6.1, U1.19 (ADC6)
unnamed: ADC7.1, U1.22 (ADC7)
unnamed: AREF.1, U1.20 (AREF)
RX: PD0.1, U1.30 (PD0)
SCK: ISCP.3, U1.17 (PB5)
TX: PD1.1, U1.31 (PD1)
XTAL1: C4.1, U1.7 (PB6), X1.1, X2.1, X3.1
XTAL2: C5.1, U1.8 (PB7), X1.3, X2.2, X3.3

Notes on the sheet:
Pick one.
LED FX
Zodiac Synth
Cancer
SATAN'S CYCLE WORKS
